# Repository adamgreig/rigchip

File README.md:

# rigchip

connects your CHIP to your RIG

runs off rig 12V, audio in/out, serial in/out, PTT/SQL in/out

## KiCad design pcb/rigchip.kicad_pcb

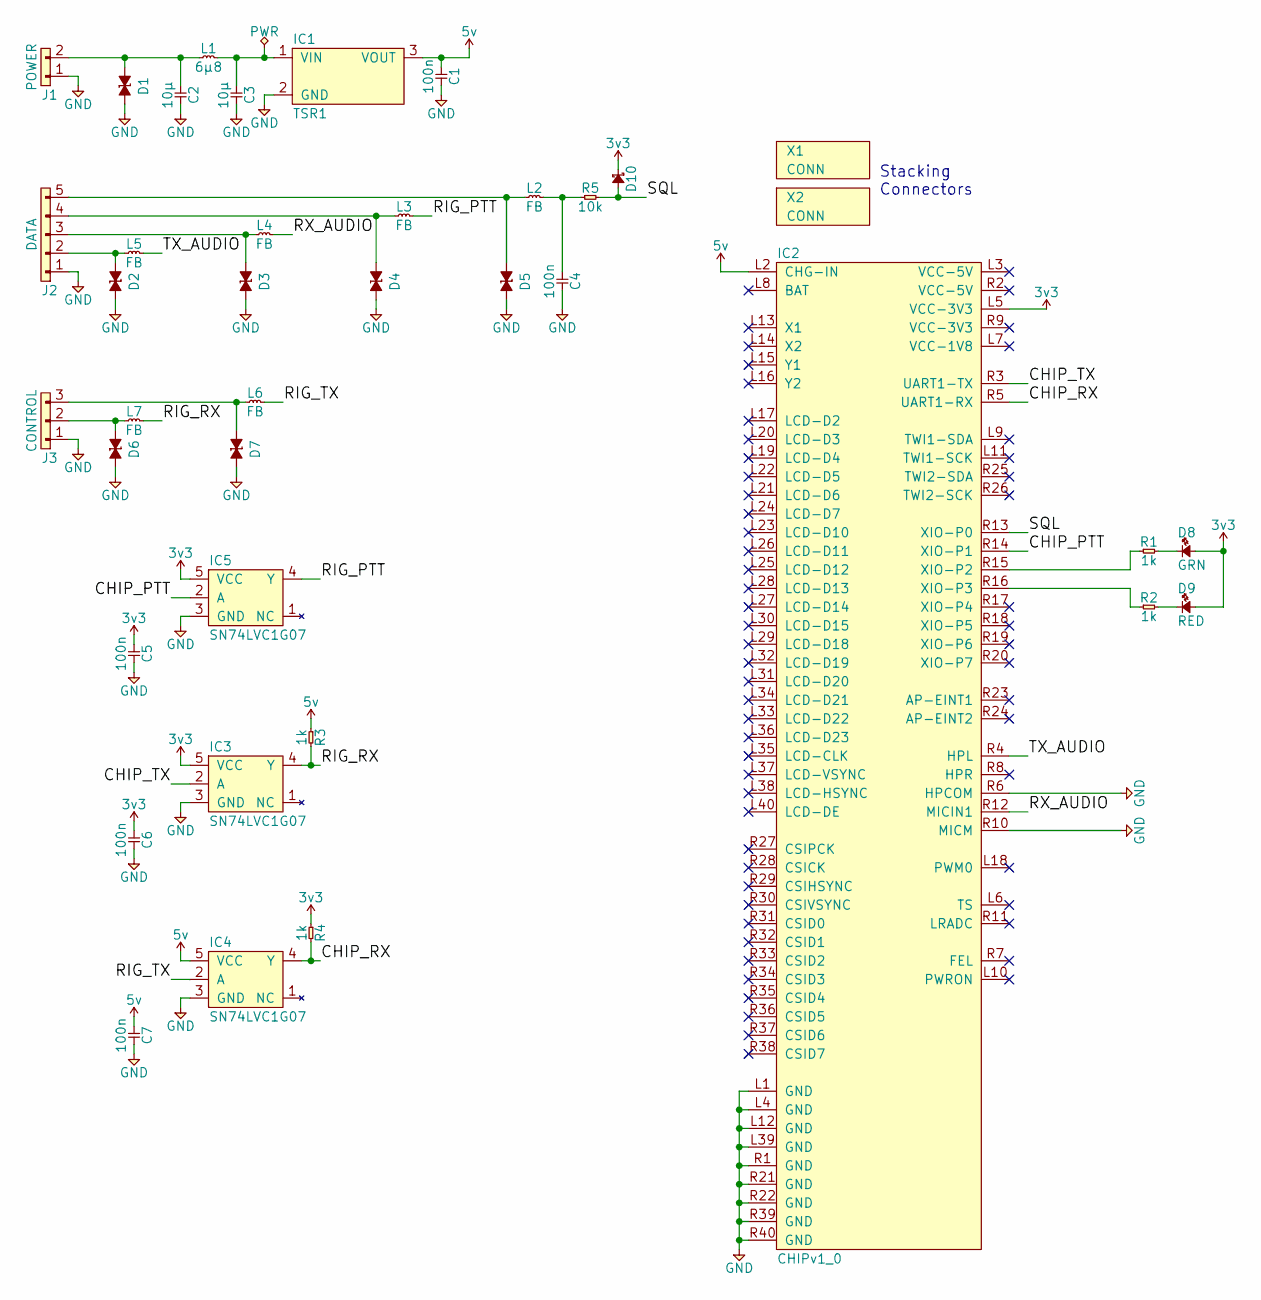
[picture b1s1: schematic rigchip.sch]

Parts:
C1, C4, C5, C6, C7: 100n; 0603
C2, C3: 10µ; 1206
D1, D2, D3, D4, D5, D6, D7: ESD_DIODE; 0402; Farnell 2368169
D8: GRN; 0603-LED
D9: RED; 0603-LED
D10: 0603-LED
IC1: TSR1; Farnell 1696320
IC2: CHIPv1_0
IC3, IC4, IC5: SN74LVC1G07; SOT-23-5; Farnell 1102969
J1: POWER; S02B-PASK-2
J2: DATA; S05B-PASK-2
J3: CONTROL; S03B-PASK-2
L1: 6µ8; TYS5040; Farnell 2292530
L2, L3, L4, L5, L6, L7: FB; 0603
R1, R2, R3, R4: 1k; 0603
R5: 10k; 0603
X1, X2: CONN; Farnell 1569230

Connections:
3v3: C5.1, C6.1, D8.2, D9.2, D10.1, IC2.L5 (VCC-3V3), IC3.5 (VCC), IC5.5 (VCC), R4.1
5v: C1.1, C7.1, IC1.3 (VOUT), IC2.L2 (CHG-IN), IC4.5 (VCC), R3.1
/CHIP_PTT: IC2.R14 (XIO-P1), IC5.2 (A)
/CHIP_RX: IC2.R5 (UART1-RX), IC4.4 (Y), R4.2
/CHIP_TX: IC2.R3 (UART1-TX), IC3.2 (A)
/RIG_PTT: IC5.4 (Y), L3.2
/RIG_RX: IC3.4 (Y), L7.2, R3.2
/RIG_TX: IC4.2 (A), L6.2
/RX_AUDIO: IC2.R12 (MICIN1), L4.2
/SQL: D10.2, IC2.R13 (XIO-P0), R5.2
/TX_AUDIO: IC2.R4 (HPL), L5.2
GND: C1.2, C2.2, C3.2, C4.2, C5.2, C6.2, C7.2, D1.2, D2.2, D3.2, D4.2, D5.2, D6.2, D7.2, IC1.2 (GND), IC2.L1 (GND), IC2.L4 (GND), IC2.L12 (GND), IC2.L39 (GND), IC2.R1 (GND), IC2.R6 (HPCOM), IC2.R10 (MICM), IC2.R21 (GND), IC2.R22 (GND), IC2.R39 (GND), IC2.R40 (GND), IC3.3 (GND), IC4.3 (GND), IC5.3 (GND), J1.1, J2.1, J3.1
unnamed: C2.1, D1.1, J1.2, L1.1
unnamed: C3.1, IC1.1 (VIN), L1.2
unnamed: C4.1, L2.2, R5.1
unnamed: D2.1, J2.2, L5.1
unnamed: D3.1, J2.3, L4.1
unnamed: D4.1, J2.4, L3.1
unnamed: D5.1, J2.5, L2.1
unnamed: D6.1, J3.2, L7.1
unnamed: D7.1, J3.3, L6.1
unnamed: D8.1, R1.2
unnamed: D9.1, R2.2
unnamed: IC2.R15 (XIO-P2), R1.1
unnamed: IC2.R16 (XIO-P3), R2.1

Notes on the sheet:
Stacking Connectors

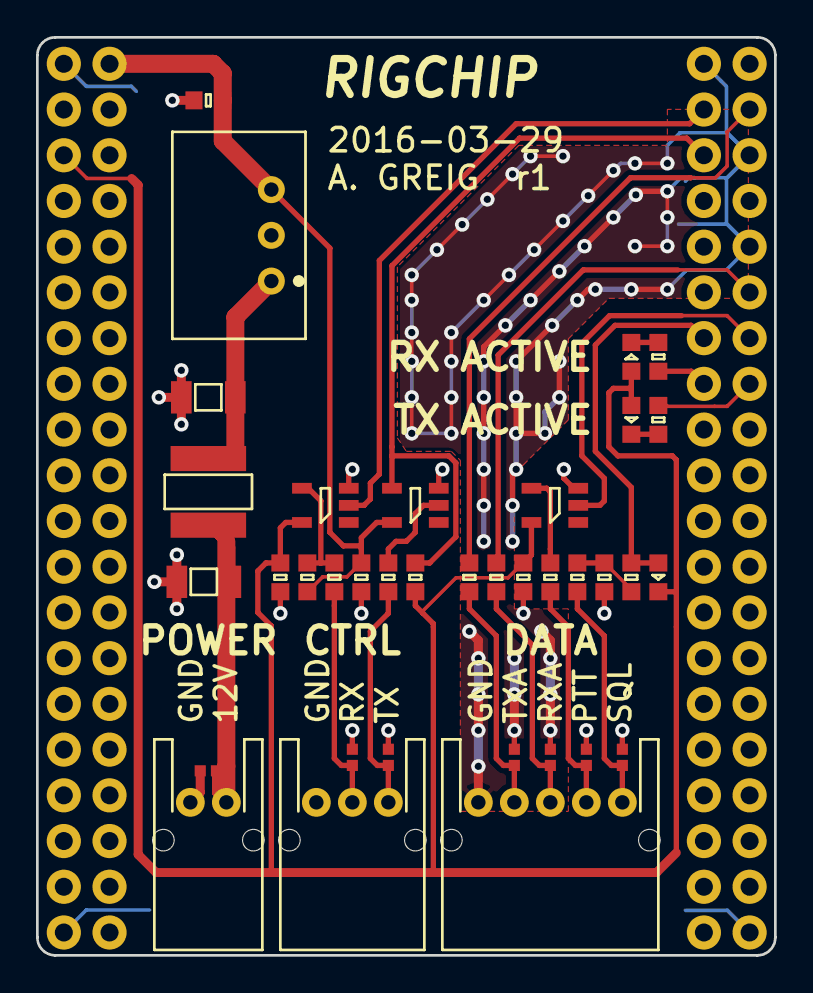
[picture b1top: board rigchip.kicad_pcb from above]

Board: 2 copper layers, 41.0 x 51.0 mm, 37 parts (0 on the bottom side), 25 nets.

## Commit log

2016-03-27 add first go at schematic
2016-03-27 first go at routing
2016-03-27 reroute, no more tracks underneath and nice shielding
2016-03-27 shrink pcb to header size
2016-03-27 add buffers to cat control
2016-03-27 update png rendering
2016-03-27 slight reroute of 3v3 net
2016-03-27 more tweaking
2016-03-27 add part number for smps
2016-03-29 LEDs to sink, driver on PTT, zener+R on SQL, reroute
2016-03-29 gerbers to manufacturing
2016-03-30 add farnell #s
2016-03-30 add stickerbom
2016-10-01 add photo
2016-10-01 add new photo
